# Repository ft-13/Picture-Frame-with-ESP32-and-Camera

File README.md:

# Picture-Frame-with-ESP32-and-Camera

The picture frame consists of Firebeetle2 (ESP32-S3) with OV2640 camera, epaper display, powerbank and a self-desined carrier PCB. The whole electronic is mounted on a 3D printed insert. There are 3 Hall sensors attached to the wood of picture frame: top, bottom left and bottom right. µSD card shield is mounted to the carrier PCB and makes it possible to save the camera picture or to load a picture. Using a magnet triggers one of the three Hall sensors and wakes up ESP32 from deep sleep. When the top Hall sensor is triggered, the picture frame takes a picture and sends it to the epeaper and the µSD card. If the left or right sensor is triggered, the previous or next image is loaded from the µSD card to the epeaper display.  
  
Special thanks go to my wife, who has always been very patient with my handicrafts :)

## Software

## Hardware

### BOM
Part | Description | Link 
--- | --- | ---
Firebeetle2 | ESP32-S3 8MB PSRAM and OV2640 camera | [dfrobot link](https://www.dfrobot.com/product-2677.html)
IT8951 display HAT | - | [Waveshare link](https://www.waveshare.com/9.7inch-e-paper-hat.htm)
epaper display | 1200x825, 9.7inch | [Waveshare datasheet](https://www.waveshare.com/w/upload/f/ff/9.7inch_E-paper_Specification.PDF)
µSD shield | D1 mini shield adapter | [AZ delivery link](https://www.az-delivery.de/products/micro-sd-card-adapter-shield)
Hall sensors | DRV5032FA TI | [TI datasheet](https://www.ti.com/lit/ds/symlink/drv5032.pdf?ts=1704351535372&ref_url=https%253A%252F%252Fwww.google.com%252F)
Analog Switch | TS3A5018PW TI | [TI datasheet](https://www.ti.com/lit/ds/symlink/ts3a5018.pdf?ts=1704375672641&ref_url=https%253A%252F%252Fwww.google.com%252F)
Powerbank | Charmast 26800mAh | [Amazon link](https://www.amazon.de/Charmast-Powerbank-Ladeger%C3%A4t-Eing%C3%A4ngen-Smartphones-Schwarz/dp/B073FJ9X2J)
Picture frame | Ikea black 21x30 cm | [Ikea link](https://www.ikea.com/de/de/p/ribba-rahmen-schwarz-60378396/)

### Powerbank
The powerbank has a hugh capacity of 26800mAh. When ESP32 is in deep sleep the entire electronic draws a current of <=2mA. If the current draw from powerbank is about <70mA the powerbank automatically turns off its outputs after 30 seconds. Then the electronic has no chance to power up unless the button of powerbank is pressed to switch it on again. I figured out that the powerbank has two DCDC converters: IP5306 and IP5310. Both chips can be configured via I2C. I found the I2C protocol of IP5306 on github: [github link](https://github.com/bheesma-10/IP5306_I2C) but no chance for IP5310. For IP5306 there is a register bit which can be set to tell the chip to stay on. Unfortunatelly this bit is not the same for IP5310. Why not using IP5306 instead of IP5310? Because I could get access only to I2C pins of IP5310 via charging state LEDs. The next problem is that IP5310 is responsible for battery charging.

I soldered I2C wires to the LEDs which are connected to IP5310 and tried to write to different registers and voila! Bit 7 of register 0x02 tells the chip to stay on.
What else? The powerbank on/off switch is connected to IP5306. As soon as IP5306 wakes up, it will wake up IP5310 via a transitor. Therefore I had to do some modifications on powerbank PCB. Now I can switch IP5310 off and on by pressing the power button of the powerbank (single push: ON, double push: OFF).

### Current Consumption
My goal was it that the powerbank lasts for about 1 year. Of course it depends on how many pictures do you take and how many picture do you load from µSD card.
In deep sleep mode the entire electronic (excluding powerbank) draws a current of about 344µA. Unfortunately, this is not the figure that can be used for the calculation. The IP5310 DCDC converter has a converter efficiency that drives the figure up at the end. That's why I measured the current consumption from the battery itself. The unloaded powerbank draws a current of 1.4mA and in loaded condition (334µA) the current consumption is about 2mA.
If I never took a photo, i.e. ESP32 is in deep sleep all the time, the power bank would last:
days = 26800mAh / 2mA / 24h = 558 days (1.5 years).

But lets make the calculation with some assumptions:  
(I have not yet made any exact measurements, so this is a simplified calculation)
- 1 picture per day and 2 µSD card read access' per day.
- take picture and send to display and µSD card: 300mA for 10s
- load picture from µSD card and send to display: 250mA for 8s
  
We need to know the average current consumption  
Iavg = (300mA * 10s + 250mA * 8s * 2 + 2mA * 3570s) / 3600s = 3.93mA  
to calculate how long the powerbank lasts  
days = 26800mAh / Iavg / 24h = 284 days.

## FAQ
1. Why is the carrier PCB so hugh?  
   Firebeetle2 (Camera has short flex PCB) and IT8951 cannot not be postioned on the same side, as the flex PCB of epaper fills the entire bottom side. Therefore there is no space left where the camera could see through.
2. Why did you use Firebeetle2? What's so special about?  
   The Firebeetle2 has a DCDC Converter, which can be configured over I2C and can deactivate the power of the camera, thus bringing the power consumption of the camera to null.
3. Why is the size of the camera picture (XGA 1024x768) smaller than the available size of the display (1200x825)?  
   Because the passpartout cut-out of the picture frame has nearly the size of XGA. Of course I could have bought a passpartout with a larger cut-out, which I will do next.
4. If you have already designed your own PCB, why didn't you include a charging circuit instead of struggling with the power bank?  
   I didn't do much research but I couldn't find a suitable Li-Ion charging IC with integrated boost converter and pass through function.
   I also wanted to keep the development time as short as possible and do without non-SOICs, as I soldered the components on by hand.
   And it was also fun "hacking" the powerbank.
5. Why did you decide to use Hall sensors instead of switches, proximity sensors or even gesture recognition using the camera?  
   The current consumption of the Hall sensors is a maximum of 3.5µA per sensor, as other sensor technologies cannot keep up.
   I wanted to do without electromechanical switches, as the overall picture would not have been nice for me, apart from the fact that I couldn't find any very small built-in pushbuttons.
   Gesture recognition using the ESP camera would have increased power consumption and drastically reduced battery life.
   A capacitive proximity switch consisting of e.g. an AD7151/AD7156 and a capacitive foil would certainly have worked as well, if not more elegantly, but in this case I wanted to save costs as I had the Hall sensors lying around anyway.
6. In which format are the files saved on the SD card or in which format do they have to be?  
   The recorded image is saved as raw bytes with an ascending number and the file extension .txt. The file size is always exactly 768432 bytes (1024x768 pixels and 8bit/pixel). 
7. Is there a way to view the images on the SD card on a PC and is it possible to save images other than those taken by the camera itself?  
   Yes, both are possible. It is possible with the free tool magick e.g. In the repository folder "Software/2_pic_converter" there is a self-written python tool.
   This tool converts all jpg images in a folder and stores them in an "output" folder. These can then simply be copied to the SD card (with ascending number).
   With the command "magick -depth 8 -size 1024x768 gray:files_on_sd_card.txt result.jpg" the raw bytes can be converted back into a jpg image.
   The tool is currently very simple and does not yet have any terminal arguments etc.
8. AI generated pictures?  
   The next upgrade will be for my Raspberry Pi server to generate an image once a day from an AI on the internet and then send it to the picture frame via Wifi.

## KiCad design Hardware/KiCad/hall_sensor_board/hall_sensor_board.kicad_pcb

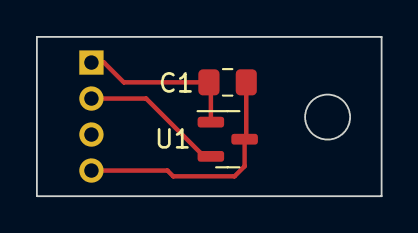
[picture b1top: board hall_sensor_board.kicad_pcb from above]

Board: 2 copper layers, 19.2 x 8.9 mm, 3 parts (1 on the bottom side), 3 nets.

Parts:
C1: 100n; C_0805_2012Metric_Pad1.18x1.45mm_HandSolder
J1: Conn_01x04_Pin; PinHeader_1x04_P2.00mm_Horizontal
U1: DRV5032FA; SOT-23

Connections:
+3.3V: C1.1, J1.1, U1.1 (VCC)
GND: C1.2, J1.4, U1.3 (GND)
unnamed: J1.2, U1.2 (OUT)

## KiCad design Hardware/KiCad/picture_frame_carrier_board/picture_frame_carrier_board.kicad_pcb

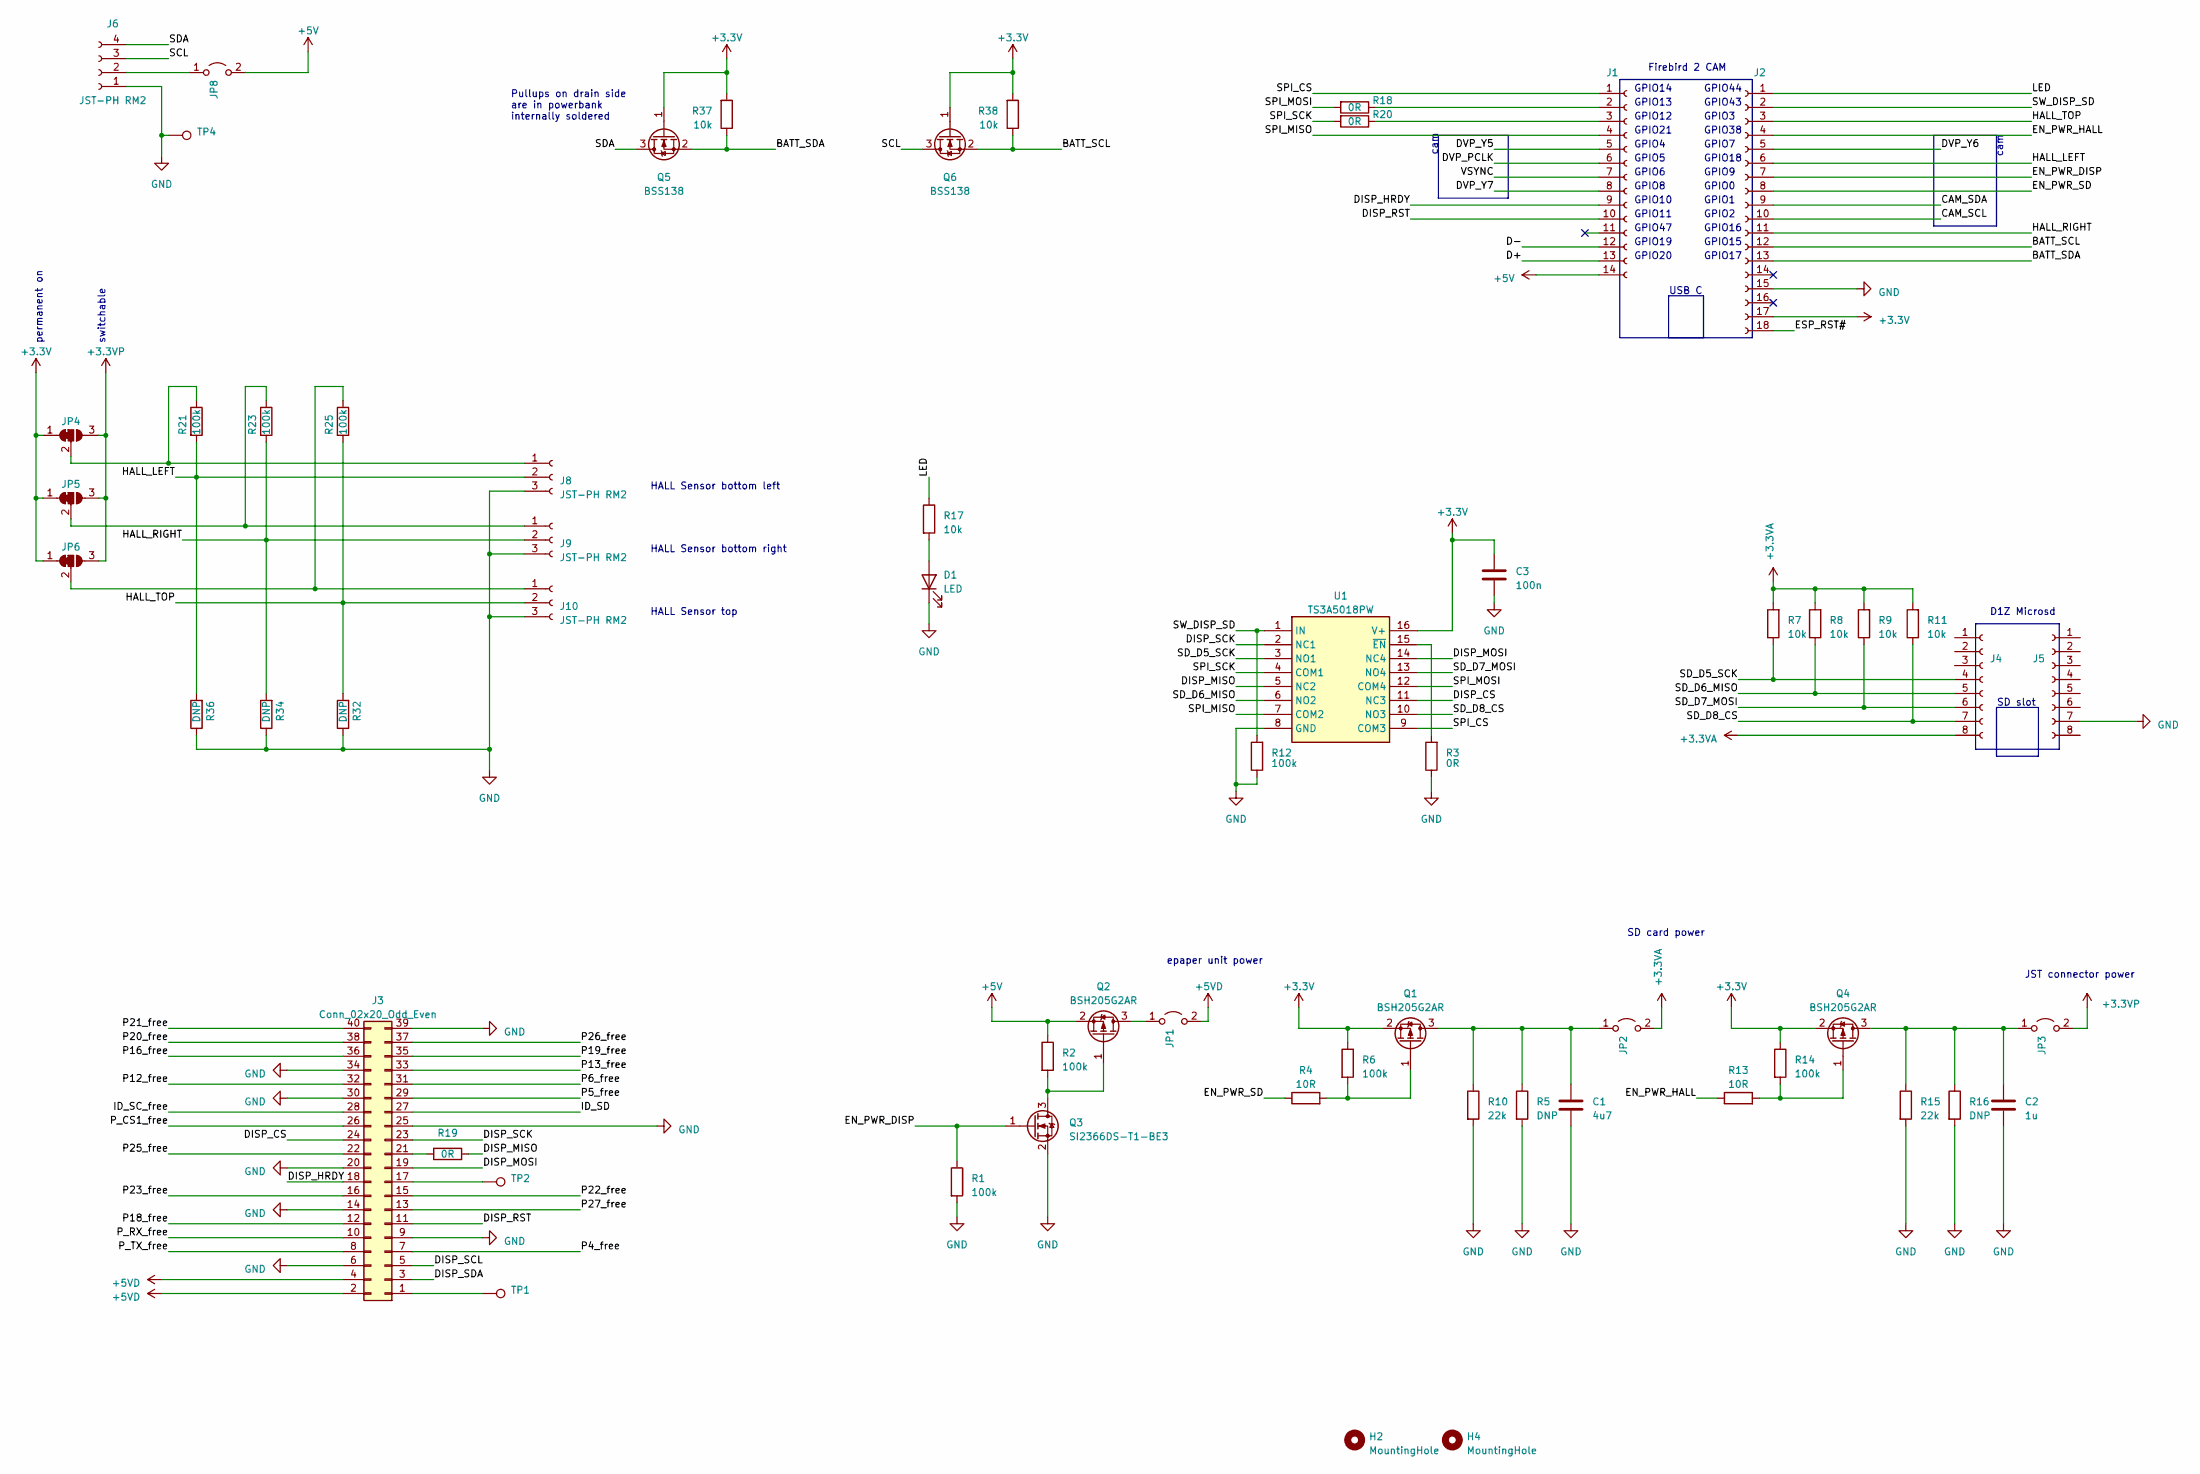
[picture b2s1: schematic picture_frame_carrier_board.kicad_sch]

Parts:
C1: 4u7; C_0805_2012Metric_Pad1.18x1.45mm_HandSolder
C2: 1u; C_0805_2012Metric_Pad1.18x1.45mm_HandSolder
C3: 100n; C_0805_2012Metric_Pad1.18x1.45mm_HandSolder
D1: LED; LED_0603_1608Metric_Pad1.05x0.95mm_HandSolder
H2, H4: MountingHole; MountingHole_2.7mm_M2.5_DIN965
J1: Conn_01x14_Socket; PinSocket_1x14_P2.54mm_Vertical
J2: Conn_01x18_Socket; PinSocket_1x18_P2.54mm_Vertical
J3: Conn_02x20_Odd_Even; bkl_10122235
J4, J5: Conn_01x08_Socket; PinSocket_1x08_P2.54mm_Vertical
J6: JST-PH RM2; JST_PH_S4B-PH-K_1x04_P2.00mm_Horizontal
J8, J9, J10: JST-PH RM2; JST_PH_S3B-PH-K_1x03_P2.00mm_Horizontal
JP1, JP2, JP3, JP8: Jumper_2_Open; PinHeader_1x02_P2.54mm_Vertical
JP4, JP5, JP6: SolderJumper_3_Bridged12; SolderJumper-3_P1.3mm_Bridged12_Pad1.0x1.5mm_NumberLabels
Q1, Q2, Q4: BSH205G2AR; SOT-23
Q3: SI2366DS-T1-BE3; SOT-23
Q5, Q6: BSS138; SOT-23
R1, R2, R6, R12, R14, R21, R23, R25: 100k; R_0805_2012Metric_Pad1.20x1.40mm_HandSolder
R3, R18, R19, R20: 0R; R_0805_2012Metric_Pad1.20x1.40mm_HandSolder
R4, R13: 10R; R_0805_2012Metric_Pad1.20x1.40mm_HandSolder
R5, R16, R32, R34, R36: DNP; R_0805_2012Metric_Pad1.20x1.40mm_HandSolder
R7, R8, R9, R11, R17, R37, R38: 10k; R_0805_2012Metric_Pad1.20x1.40mm_HandSolder
R10, R15: 22k; R_0805_2012Metric_Pad1.20x1.40mm_HandSolder
TP1, TP2: TestPoint; TestPoint_Pad_1.5x1.5mm
TP4: TestPoint; TestPoint_THTPad_D2.5mm_Drill1.2mm
U1: TS3A5018PW; SOP65P640X120-16N; Mouser Part Number 595-TS3A5018PW

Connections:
+3.3V: C3.1, J2.17, JP4.1 (A), JP5.1 (A), JP6.1 (A), Q1.2 (S), Q4.2 (S), Q5.1 (G), Q6.1 (G), R6.1, R14.1, R37.2, R38.2, U1.16 (V+)
+3.3VA: J4.8, JP2.2 (B), R7.2, R8.2, R9.2, R11.2
+3.3VP: JP3.2 (B), JP4.3 (B), JP5.3 (B), JP6.3 (B)
+5V: J1.14, JP8.2 (B), Q2.2 (S), R2.1
+5VD: J3.2, J3.4, JP1.2 (B)
/BATT_SCL: J2.12, Q6.2 (S), R38.1
/BATT_SDA: J2.13, Q5.2 (S), R37.1
/CAM_SCL: J2.10
/CAM_SDA: J2.9
/D+: J1.13
/D-: J1.12
/DISP_CS: J3.24, U1.11 (NC3)
/DISP_HRDY: J1.9, J3.18
/DISP_MISO: R19.1, U1.5 (NC2)
/DISP_MOSI: J3.19, U1.14 (NC4)
/DISP_RST: J1.10, J3.11
/DISP_SCK: J3.23, U1.2 (NC1)
/DISP_SCL: J3.5
/DISP_SDA: J3.3
/DVP_PCLK: J1.6
/DVP_Y5: J1.5
/DVP_Y6: J2.5
/DVP_Y7: J1.8
/EN_PWR_DISP: J2.7, Q3.1 (G), R1.1
/EN_PWR_HALL: J2.4, R13.1
/EN_PWR_SD: J2.8, R4.1
/ESP_RST#: J2.18
/HALL_LEFT: J2.6, J8.2, R21.2, R36.2
/HALL_RIGHT: J2.11, J9.2, R23.2, R34.2
/HALL_TOP: J2.3, J10.2, R25.2, R32.2
/ID_SC_free: J3.28
/ID_SD: J3.27
/LED: J2.1, R17.1
/P4_free: J3.7
/P5_free: J3.29
/P6_free: J3.31
/P12_free: J3.32
/P13_free: J3.33
/P16_free: J3.36
/P18_free: J3.12
/P19_free: J3.35
/P20_free: J3.38
/P21_free: J3.40
/P22_free: J3.15
/P23_free: J3.16
/P25_free: J3.22
/P26_free: J3.37
/P27_free: J3.13
/P_CS1_free: J3.26
/P_RX_free: J3.10
/P_TX_free: J3.8
/SCL: J6.3, Q6.3 (D)
/SDA: J6.4, Q5.3 (D)
/SD_D5_SCK: J4.4, R7.1, U1.3 (NO1)
/SD_D6_MISO: J4.5, R8.1, U1.6 (NO2)
/SD_D7_MOSI: J4.6, R9.1, U1.13 (NO4)
/SD_D8_CS: J4.7, R11.1, U1.10 (NO3)
/SPI_CS: J1.1, U1.9 (COM3)
/SPI_MISO: J1.4, U1.7 (COM2)
/SPI_MOSI: R18.2, U1.12 (COM4)
/SPI_SCK: R20.2, U1.4 (COM1)
/SW_DISP_SD: J2.2, R12.2, U1.1 (IN)
/VSYNC: J1.7
GND: C1.2, C2.2, C3.2, D1.1 (K), J2.15, J3.6, J3.9, J3.14, J3.20, J3.25, J3.30, J3.34, J3.39, J5.7, J6.1, J8.3, J9.3, J10.3, Q3.2 (S), R1.2, R3.1, R5.2, R10.2, R12.1, R15.2, R16.2, R32.1, R34.1, R36.1, TP4.1, U1.8 (GND)
unnamed: D1.2 (A), R17.2
unnamed: J1.2, R18.1
unnamed: J1.3, R20.1
unnamed: J3.1, TP1.1
unnamed: J3.17, TP2.1
unnamed: J3.21, R19.2
unnamed: J6.2, JP8.1 (A)
unnamed: J8.1, JP4.2 (C), R21.1
unnamed: J9.1, JP5.2 (C), R23.1
unnamed: J10.1, JP6.2 (C), R25.1
unnamed: JP1.1 (A), Q2.3 (D)
unnamed: C1.1, JP2.1 (A), Q1.3 (D), R5.1, R10.1
unnamed: C2.1, JP3.1 (A), Q4.3 (D), R15.1, R16.1
unnamed: Q1.1 (G), R4.2, R6.2
unnamed: Q2.1 (G), Q3.3 (D), R2.2
unnamed: Q4.1 (G), R13.2, R14.2
unnamed: R3.2, U1.15 (~EN)

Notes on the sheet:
cam
GPIO18
GPIO7
GPIO5
JST connector power
GPIO6
GPIO15
HALL Sensor top
D1Z Microsd
GPIO44
GPIO1
GPIO2
HALL Sensor bottom right
GPIO4
GPIO47
GPIO8
SD slot
SD card power
GPIO38
Firebird 2 CAM
GPIO13
GPIO10
GPIO11
epaper unit power
GPIO9
GPIO17
GPIO3
GPIO16
HALL Sensor bottom left
GPIO12
USB C
GPIO21
permanent on
GPIO0
GPIO43
switchable
GPIO14
GPIO19
GPIO20
Pullups on drain side are in powerbank internally soldered

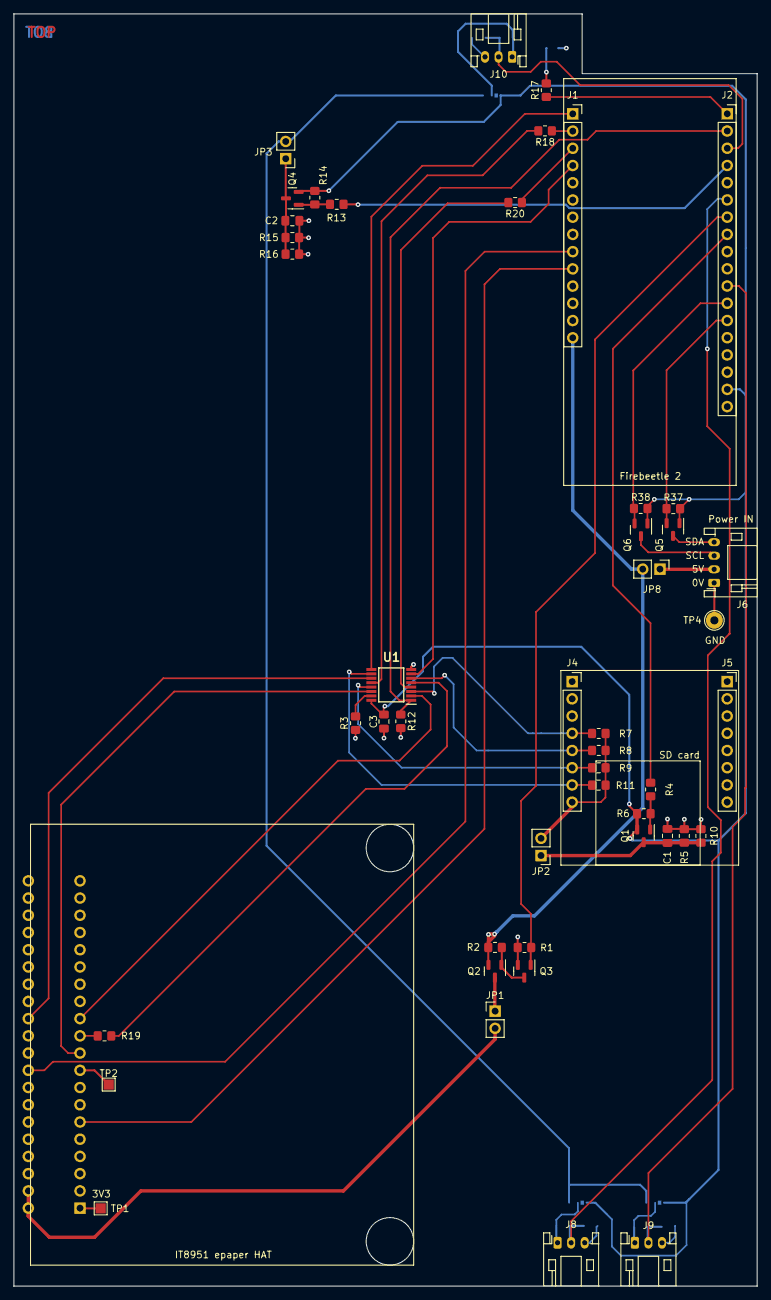
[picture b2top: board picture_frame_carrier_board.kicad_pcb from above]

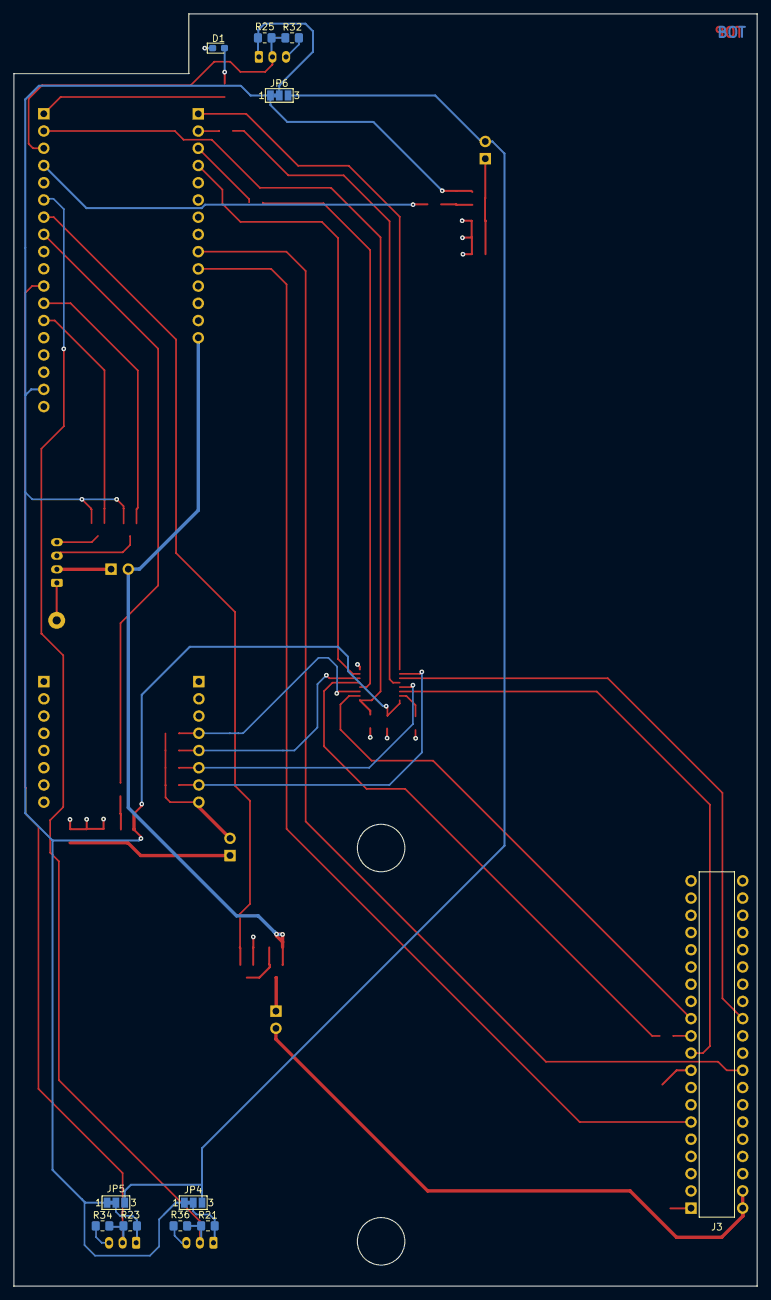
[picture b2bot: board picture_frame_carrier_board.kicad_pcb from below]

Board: 4 copper layers, 109.6 x 187.6 mm, 60 parts (11 on the bottom side), 49 nets.

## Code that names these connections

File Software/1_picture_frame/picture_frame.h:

#ifndef _PICTURE_FRAME_H_
#define _PICTURE_FRAME_H_

#define STAT_OK 1
#define STAT_ERR 0

#define BATT_IP5310_ADDRESS      0x75   // IP5310 slave address
#define BATT_IP5310_REG          0x02   // register where permanent ON bit is located
#define BATT_IP5310_VALUE        0xE0   // default value in 0x02 is 01100000; set 11100000 -> 0xE0

#define BATT_SCL                 15
#define BATT_SDA                 17

#define EN_PWR_HALL              38
#define EN_PWR_DISP              9
#define EN_PWR_SD                0

#define LED_SHOT                 44     // red LED in front panel to indicate taking picture

#define SW_DISP_SD               43     // analog switch IN pin to switch SPI signals between SD card and epaper display

// three hall sensors to
// wake up ESP32
#define HALL_TOP                  3     // take picture and send to display and save to sd card
#define HALL_LEFT                18     // get previous picture from sd card and send to display
#define HALL_RIGHT               16     // get next picture from sd card and send to display
/*#define DEEP_SLEEP_BITMASK \
((2^HALL_TOP) + \
(2^HALL_LEFT) + \
(2^HALL_RIGHT))*/
// Generate deep sleep wake up bitmask:
// Bitmask = 2^3 + 2^16 + 2^18 (3 -> GPIO3, 16 -> GPIO16, 18 -> GPIO18)
// https://randomnerdtutorials.com/esp32-external-wake-up-deep-sleep/
#define DEEP_SLEEP_BITMASK      ((1<<HALL_TOP) | (1<<HALL_LEFT) | (1<<HALL_RIGHT))

// SPI signals (µSD and epaper)
// and control signals (epaper)
#define RESET                    11
#define HRDY                     10
#define MISO                     21
#define MOSI                     13
#define SCK                      12
#define CS                       14

// 9.7 inch epaper 1200x825
// camer XGA is 1024x768
// To set smaller pic (camera XGA) to the center of epaper
#define DISP_OFFSET_X            88   // (1200 - 1024) / 2 = 88
#define DISP_OFFSET_Y            28   // (825 - 768) / 2 = 28.5


// ov2640 camera signals
#define PWDN_GPIO_NUM            -1
#define RESET_GPIO_NUM           -1
#define XCLK_GPIO_NUM            45
#define SIOD_GPIO_NUM             1
#define SIOC_GPIO_NUM             2
#define Y9_GPIO_NUM              48
#define Y8_GPIO_NUM              46
#define Y7_GPIO_NUM               8
#define Y6_GPIO_NUM               7
#define Y5_GPIO_NUM               4
#define Y4_GPIO_NUM              41
#define Y3_GPIO_NUM              40
#define Y2_GPIO_NUM              39
#define VSYNC_GPIO_NUM            6
#define HREF_GPIO_NUM            42
#define PCLK_GPIO_NUM             5


extern SPIClass spi;

#endif

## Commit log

2024-01-04 files modified
2024-01-04 modified
2024-01-04 picture added
2024-01-04 picture changed
2024-01-04 added demo video
2024-01-04 changed files
2024-01-04 demo video added
2024-01-04 video deleted
2024-01-04 video added
2024-01-04 video gif added
2024-01-05 faq in readme added
2024-01-05 spi clock, camer clock and camera frame for loop updated
